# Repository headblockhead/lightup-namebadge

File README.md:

# Lightup Namebadge

A small badge/lanyard thingy with some basic transistor logic and LEDs to light up the darkness.

Created for [Hack Club's Solder YSWS](https://solder.hackclub.com/).

## Features:
- On/Off switches (SR latch)
- Photoresistor to dim LEDs in daylight.
- Potentometer control of LED brightness, and photoresistor sensitivity.
- Schematic is provided on the back
- Says my name on the front of it!

## BOM:
- 6x LEDs
- 2x 1kΩ Resistors
- 2x 10kΩ Resistors
- 1x 220Ω resistor
- 2x (10kΩ?) Potentiometers
- 4x NPN transistors
- 1x PNP transistor
- 2x push-button
- 1x (100kΩ?) photoresistor
- 1x CR2032 battery holder

## Screenshots:

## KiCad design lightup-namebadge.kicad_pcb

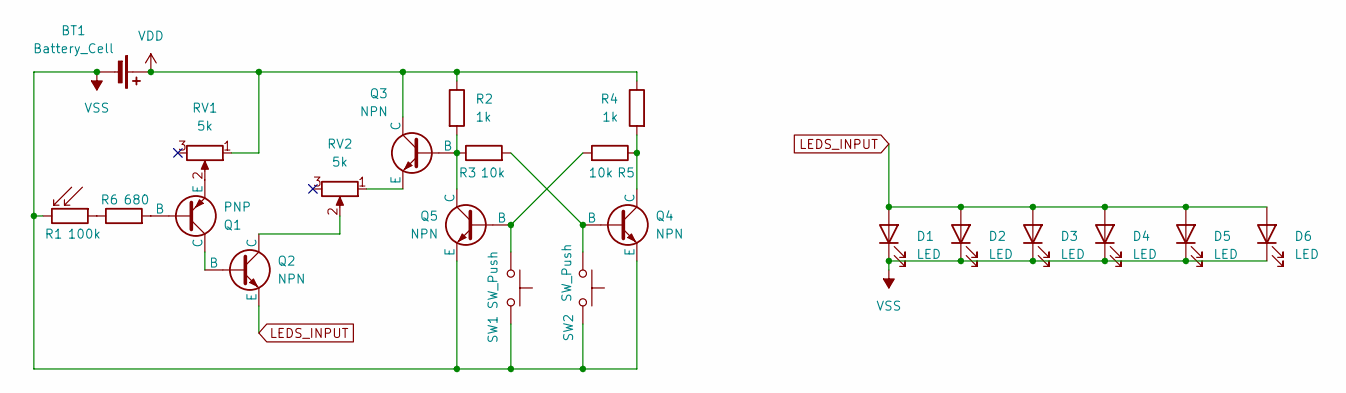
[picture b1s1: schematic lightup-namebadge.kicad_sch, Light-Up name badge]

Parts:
BT1: Battery_Cell; BatteryHolder_Keystone_3034_1x20mm
D1, D2, D3, D4, D5, D6: LED; LED_D5.0mm
Q1: PNP; TO-92L_HandSolder
Q2, Q3, Q4, Q5: NPN; TO-92L_HandSolder
R1: 100k; R_LDR_5.1x4.3mm_P3.4mm_Vertical
R2, R4: 1k; R_Axial_DIN0207_L6.3mm_D2.5mm_P7.62mm_Horizontal
R3, R5: 10k; R_Axial_DIN0207_L6.3mm_D2.5mm_P7.62mm_Horizontal
R6: 680; R_Axial_DIN0207_L6.3mm_D2.5mm_P7.62mm_Horizontal
RV1, RV2: 5k; Potentiometer_Vishay_T73YP_Vertical
SW1, SW2: SW_Push; SW_PUSH_6mm

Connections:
LEDS_INPUT: D1.2 (A), D2.2 (A), D3.2 (A), D4.2 (A), D5.2 (A), D6.2 (A), Q2.3 (E)
unnamed: Q1.2 (B), R6.2
unnamed: Q1.1 (C), Q2.2 (B)
unnamed: Q1.3 (E), RV1.2
unnamed: Q2.1 (C), RV2.2
unnamed: Q3.2 (B), Q5.1 (C), R2.2, R3.1
unnamed: Q3.3 (E), RV2.1
unnamed: Q4.2 (B), R3.2, SW2.1
unnamed: Q4.1 (C), R4.2, R5.1
unnamed: Q5.2 (B), R5.2, SW1.1
unnamed: R1.1, R6.1
VDD: BT1.1 (+), Q3.1 (C), R2.1, R4.1, RV1.1
VSS: BT1.2 (-), D1.1 (K), D2.1 (K), D3.1 (K), D4.1 (K), D5.1 (K), D6.1 (K), Q4.3 (E), Q5.3 (E), R1.2, SW1.2, SW2.2

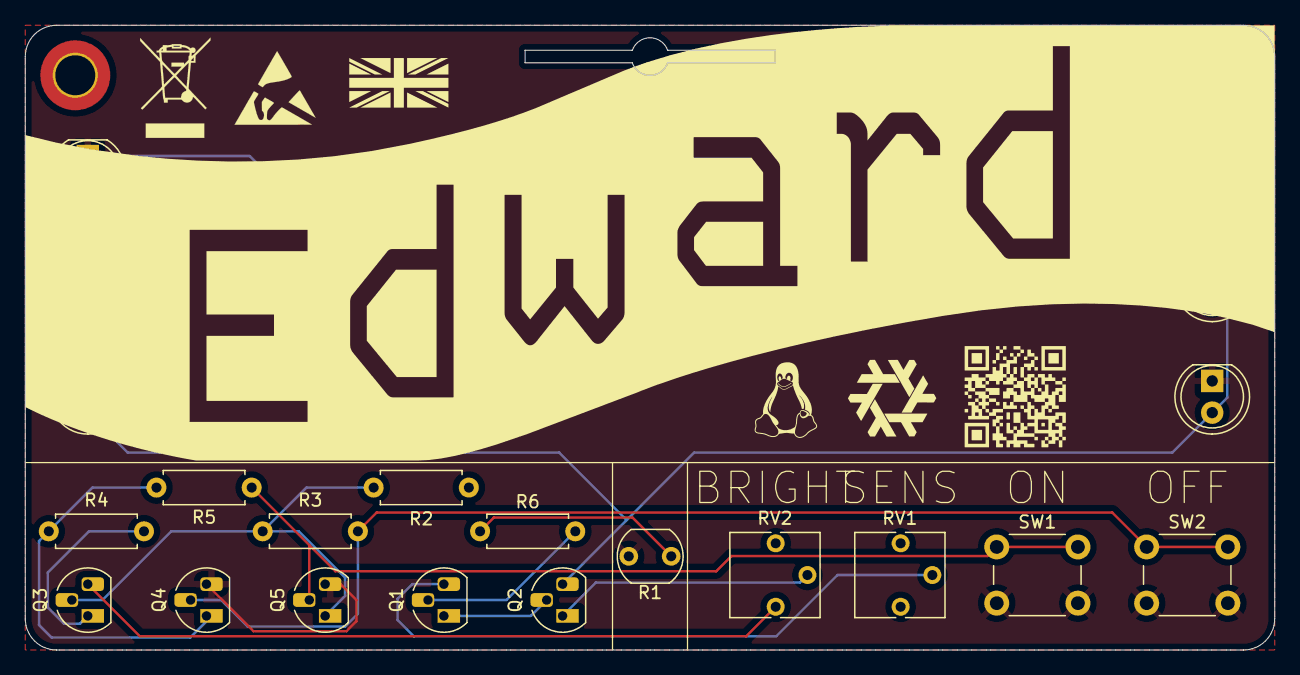
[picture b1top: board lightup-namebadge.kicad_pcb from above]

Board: 2 copper layers, 100.0 x 50.0 mm, 22 parts (1 on the bottom side), 13 nets.

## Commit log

2025-05-30 v1 of lightup-namebadge
2025-05-30 fix: disconnect pin 3 of RV1 from VSS to save power
2025-05-30 docs(README): add readme
2025-05-30 feat: add gerbers
2025-05-31 Create LICENSE
2025-06-19 fix: new resistor values and more thermal relif for battery connector
